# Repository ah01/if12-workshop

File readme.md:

Materials for Arduino workshop on conference InstallFest 2012

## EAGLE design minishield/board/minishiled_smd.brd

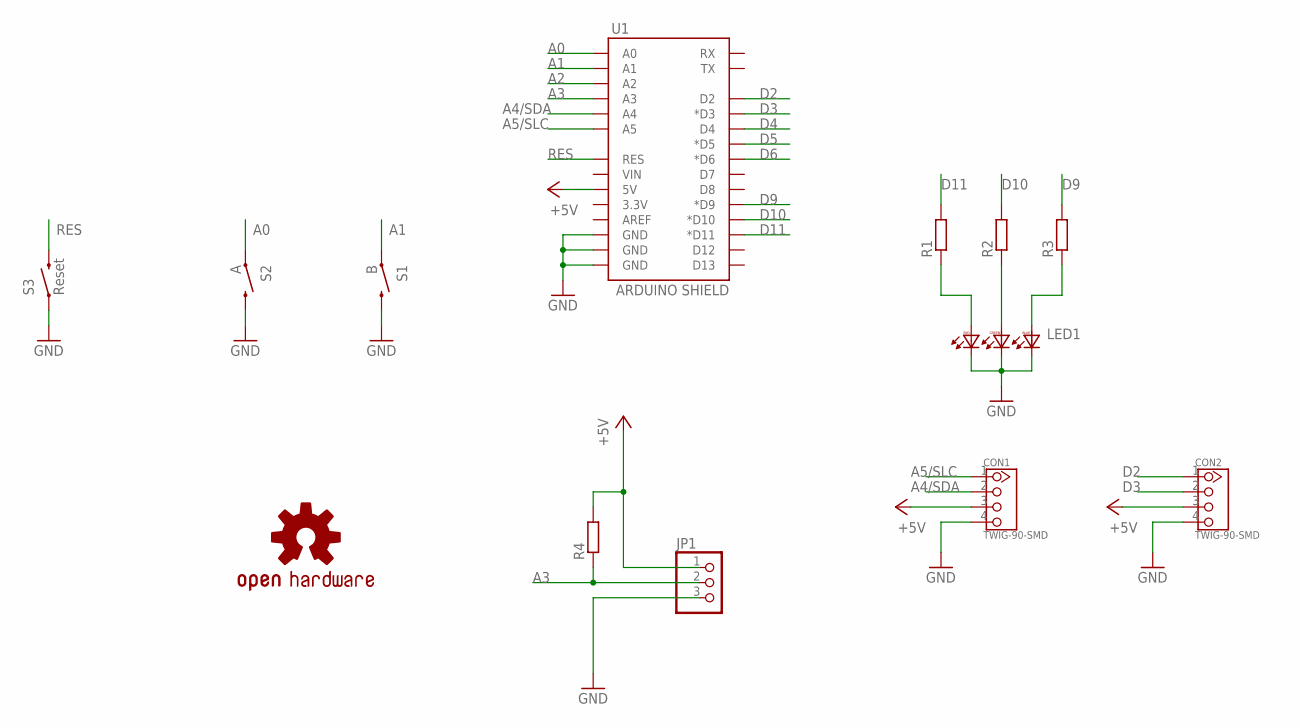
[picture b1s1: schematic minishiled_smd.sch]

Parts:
CON1, CON2: TWIG-90-SMD
JP1: PINHD-1X3; 1X03
LED1: LED-RGB-PLCC6; PLCC6-RAW
R1, R2, R3, R4: R-EU_R1206; R1206
S1: B; TACTILE_SWITCH_TALL
S2: A; TACTILE_SWITCH_TALL
S3: Reset; TACTILE-SWITCH-1101NE
U1: ARDUINO SHIELD; DUEMILANOVE_VIAS
U$1: LOGO-OSH

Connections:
+5V: CON1.3, CON2.3, JP1.1, R4.2, U1.5V
A0: S2.A2 (1), U1.A0
A1: S1.A2 (1), U1.A1
A2: U1.A2
A3: JP1.2, R4.1, U1.A3
A4/SDA: CON1.2, U1.A4
A5/SLC: CON1.1, U1.A5
D2: CON2.1, U1.D2
D3: CON2.2, U1.D3 (*D3)
D4: U1.D4
D5: U1.D5 (*D5)
D6: U1.D6 (*D6)
D9: R3.2, U1.D9 (*D9)
D10: R2.2, U1.D10 (*D10)
D11: R1.2, U1.D11 (*D11)
GND: CON1.4, CON2.4, JP1.3, LED1.4 (BC), LED1.5 (GC), LED1.6 (RC), S1.B2 (2), S2.B2 (2), S3.P$1 (1), U1.GND@0 (GND), U1.GND@1 (GND), U1.GND@2 (GND)
unnamed: LED1.3 (RA), R1.1
unnamed: LED1.2 (GA), R2.1
unnamed: LED1.1 (BA), R3.1
RES: S3.P$2 (2), U1.RES

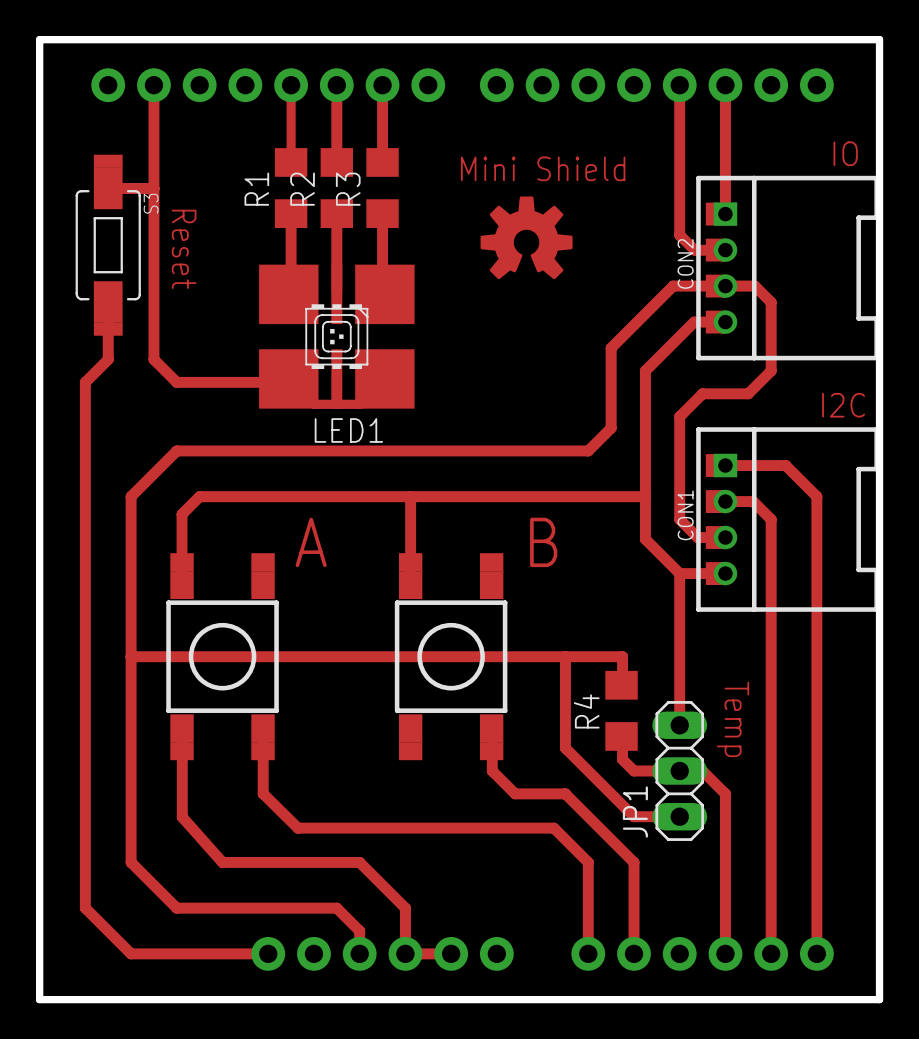
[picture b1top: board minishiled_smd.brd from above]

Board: 2 copper layers, 46.7 x 53.3 mm, 13 parts (0 on the bottom side), 16 nets.

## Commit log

2012-03-02 Add minishield board files.
2012-03-02 Add test sketch for minishield.
2012-03-02 Ignore Eagle temp files.
2012-03-04 Add extension port tests.
2012-03-04 Add example sketches.

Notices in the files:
parts and their libraries:
SparkFun-Boards: Licensing: CC v3.0 Share-Alike You are welcome to use this library for commercial purposes.
